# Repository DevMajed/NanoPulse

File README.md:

# NanoPulse – A Precision 24-bit Pulse Capture Digitizer
Hardware project — firmware will live in another repo.

# Purpose & Use Cases
**NanoPulse** is a 2-channel, 24-bit, trigger-synchronized digitizer for **µs-scale pulses**. It gives a cleaner, more deterministic “scope view” with higher vertical resolution, lower drift, and easy automation in a tiny form factor.
- What: 24-bit, 2-channel digitizer for µs pulses (hundreds of kHz BW).  
- For: labs validating pulse shape, battery DCIR, and rail transients, Ultrasonic/sonar echo logger (lab/test-tank, 40–300 kHz)
- Why: cleaner data than 8–12-bit scopes, deterministic trigger, tiny + scriptable.

---

# Purpose & Use Cases

**NanoPulse** delivers a deterministic external-trigger capture path tuned for **hundreds of kHz BW** and **µs pulses**.

## 1) Scope-replacement for pulsed benches (µs pulses)
**What it solves**  
Verify the **actual** applied pulse (rise/fall, overshoot, flatness, droop) without wheeling in a DSO.

**Who it’s for**  
Power-electronics / microwave labs, bench integrators.

**Hook**  
24-bit depth + clean CNV trigger reveals subtle flat-top errors and overshoot that 8–12-bit scopes smear.

**Connect (minimal extras)**
- `Sense Out (BNC/SMA)` → `NanoPulse IN` *(use a simple divider if needed)*
- `External Trigger (DDG/TTL)` → `TRIG IN` *(optional on-board 50 Ω)*

**Quick checklist**
- [ ] Minimal overshoot/ringing  
- [ ] Flat-top ripple/droop within spec  
- [ ] Repeated pulses overlay tightly (deterministic timing)

**Output**  
CSV + plots via simple Python scripts.

---

## 2) Battery / Cell DCIR & Pulsed-Load Logging
**What it solves**  
Clean capture of **voltage droop and relaxation** during programmed load pulses (≈10 µs–100 ms) for DCIR and transient analysis.

**Who it’s for**  
Battery research labs, EV startups, QA.

**Hook**  
High dynamic range + low drift → clearer droop and recovery curves than a typical scope; easy CSV export.

**Connect (minimal extras)**
- `Cell V` → `NanoPulse IN` *(add a 2-resistor divider if V exceeds input range)*  
- Optional: `Shunt V (current)` → `CH2`

**Quick checklist**
- [ ] Stable ΔV (droop) across repeats  
- [ ] Consistent relaxation time constants (τ)  
- [ ] Negligible baseline drift on long captures

**Output**  
CSV of V(t) (and I(t) if used), with auto-computed DCIR and τ.

---

## 3) Power-Rail / Load-Step Transient Verification (PMIC/LDO)
**What it solves**  
Measures **droop, settling time, and small ripple** on precision rails during load steps (≈100 µs–10 ms).

**Who it’s for**  
Analog/PMIC teams, embedded HW labs.

**Hook**  
24-bit vertical resolution + drift stability → see micro-ripple/settling that scopes miss.

**Connect (minimal extras)**
- `Rail` → `NanoPulse IN` *(use a small divider if needed)*  
- `Load-Step Trigger` → `TRIG IN` *(or use Manual Trigger)*

**Quick checklist**
- [ ] Droop within budget  
- [ ] No excessive undershoot/overshoot  
- [ ] Settling to ±x% within target time

**Output**  
CSV + auto-generated plot with annotated droop/settling metrics.

---

## 4) Ultrasonic / Sonar Echo Logging (lab/test-tank, 40–300 kHz)

**What it solves**  
Time-locked recording of **echo waveforms** for TOF, envelope, and multipath analysis—without touching OEM sonar firmware.

**Who it’s for**  
University acoustics/ultrasound labs, NDT benches, AUV/ROV research groups.

**Hook**  
24-bit dynamic range + deterministic trigger resolves **weak echoes** and small envelope changes better than typical 12–16-bit scopes.

**Connect (minimal extras)**
- `Receiver/Baseband Out (BNC/SMA)` → `NanoPulse IN` *(stay within input range or use a simple divider)*  
- `TX Sync/Trigger (TTL)` → `TRIG IN` *(optional on-board 50 Ω)*

**Quick checklist**
- [ ] Stable ping-to-echo timing (TOF) across repeats  
- [ ] Envelope + multipath clearly visible in the 40–300 kHz band  
- [ ] No clipping; baseline drift negligible on long logs

**Output**  
CSV of echo segments + optional envelope/spectrogram plots via Python.

---

# Headline Specs
- **ADC:** Analog Devices **AD4630-24**, up to **2 MSPS**, 24-bit  
- **Channels:** 2 differential, fully-differential amp (FDA) driven  
- **Trigger:** external **TRIG IN** → Schmitt-conditioned → CNV; **Manual Trigger** pad  
- **I/O domains:** **1.8 V** (ADC) and **3.3 V** (MCU) with level translators  
- **Reference:** **LTC6655-5** low-noise, low-drift  
- **Rails:** **LT3042** (+5.4 V), **LT3093** (−5.4 V), **LT1763** (1.8 V & 3.3 V)  
- **Configurable 50 Ω trigger termination** for DDG/coax use (DNP by default)

**Bandwidth envelope (typical build)**
- Usable analog BW: ~**300–600 kHz** (tunable via RCs)
- Practical “clean shape” pulse widths: **≥ 5–10 µs** (2 MSPS sampling)
- **Detect-only minimum pulse:** ~**1–2 µs** (1–2 samples)

---

# Design Highlights (Decisions & Rationale)
- **Anti-alias vs. settling (µs pulses in mind):** modest input Rs (~54 Ω) and small caps (≈1–2.7 nF) around the FDA target a **few-hundred-kHz to ~1 MHz** shaping—enough to see µs edges while improving settling and noise.
- **Low-drift reference path:** **LTC6655-5** with **10 µF + 0.1 µF** close to ADC REF minimizes baseline wander in long captures.
- **Trigger integrity:** External TRIG goes through a **Schmitt buffer + enable/OR logic** to produce a crisp **CNV**; **50 Ω** termination is **optional** for DDG/coax use.
- **Signal integrity at the converter:** **33 Ω series** per ADC input leg for damping; **22–33 Ω** on **CNV** after level translation to tame edges.
- **Clean domain split:** Translators isolate the quiet **1.8 V ADC** domain from **3.3 V MCU**, enabling fast SPI and **BUSY** handshaking.

---

## Trigger Modes
- **External-coax (DDG):** populate 50 Ω at TRIG IN; QC/DDG drives a matched line.  
- **Local-logic:** leave 50 Ω DNP; CNV is driven via translator with a **22–33 Ω** series resistor.

---

## Bring-Up Checklist
- **Power-only:** verify +5.4 V, −5.4 V, +3.3 V, +1.8 V rails; REF ≈ 5.000 V.  
- **CNV source:** confirm 3.3 V at Schmitt output and **1.8 V** at ADC CNV.  
- **Zero-volt short noise:** short IN+ to IN− at SMA; log RMS code spread.  
- **Step/edge:** feed a known step; confirm minimal ringing and proper settling.  
- **Drift:** shorted input, log ≥1 h; expect very low baseline drift.

---

## Safety & Limits
- Keep inputs **within safe range** (use passive dividers when needed).  
- Target content **≤ ~1 MHz** and **µs-scale** pulses.  
- For **ns edges/RF**, use a high-BW DSO/GHz digitizer.

---

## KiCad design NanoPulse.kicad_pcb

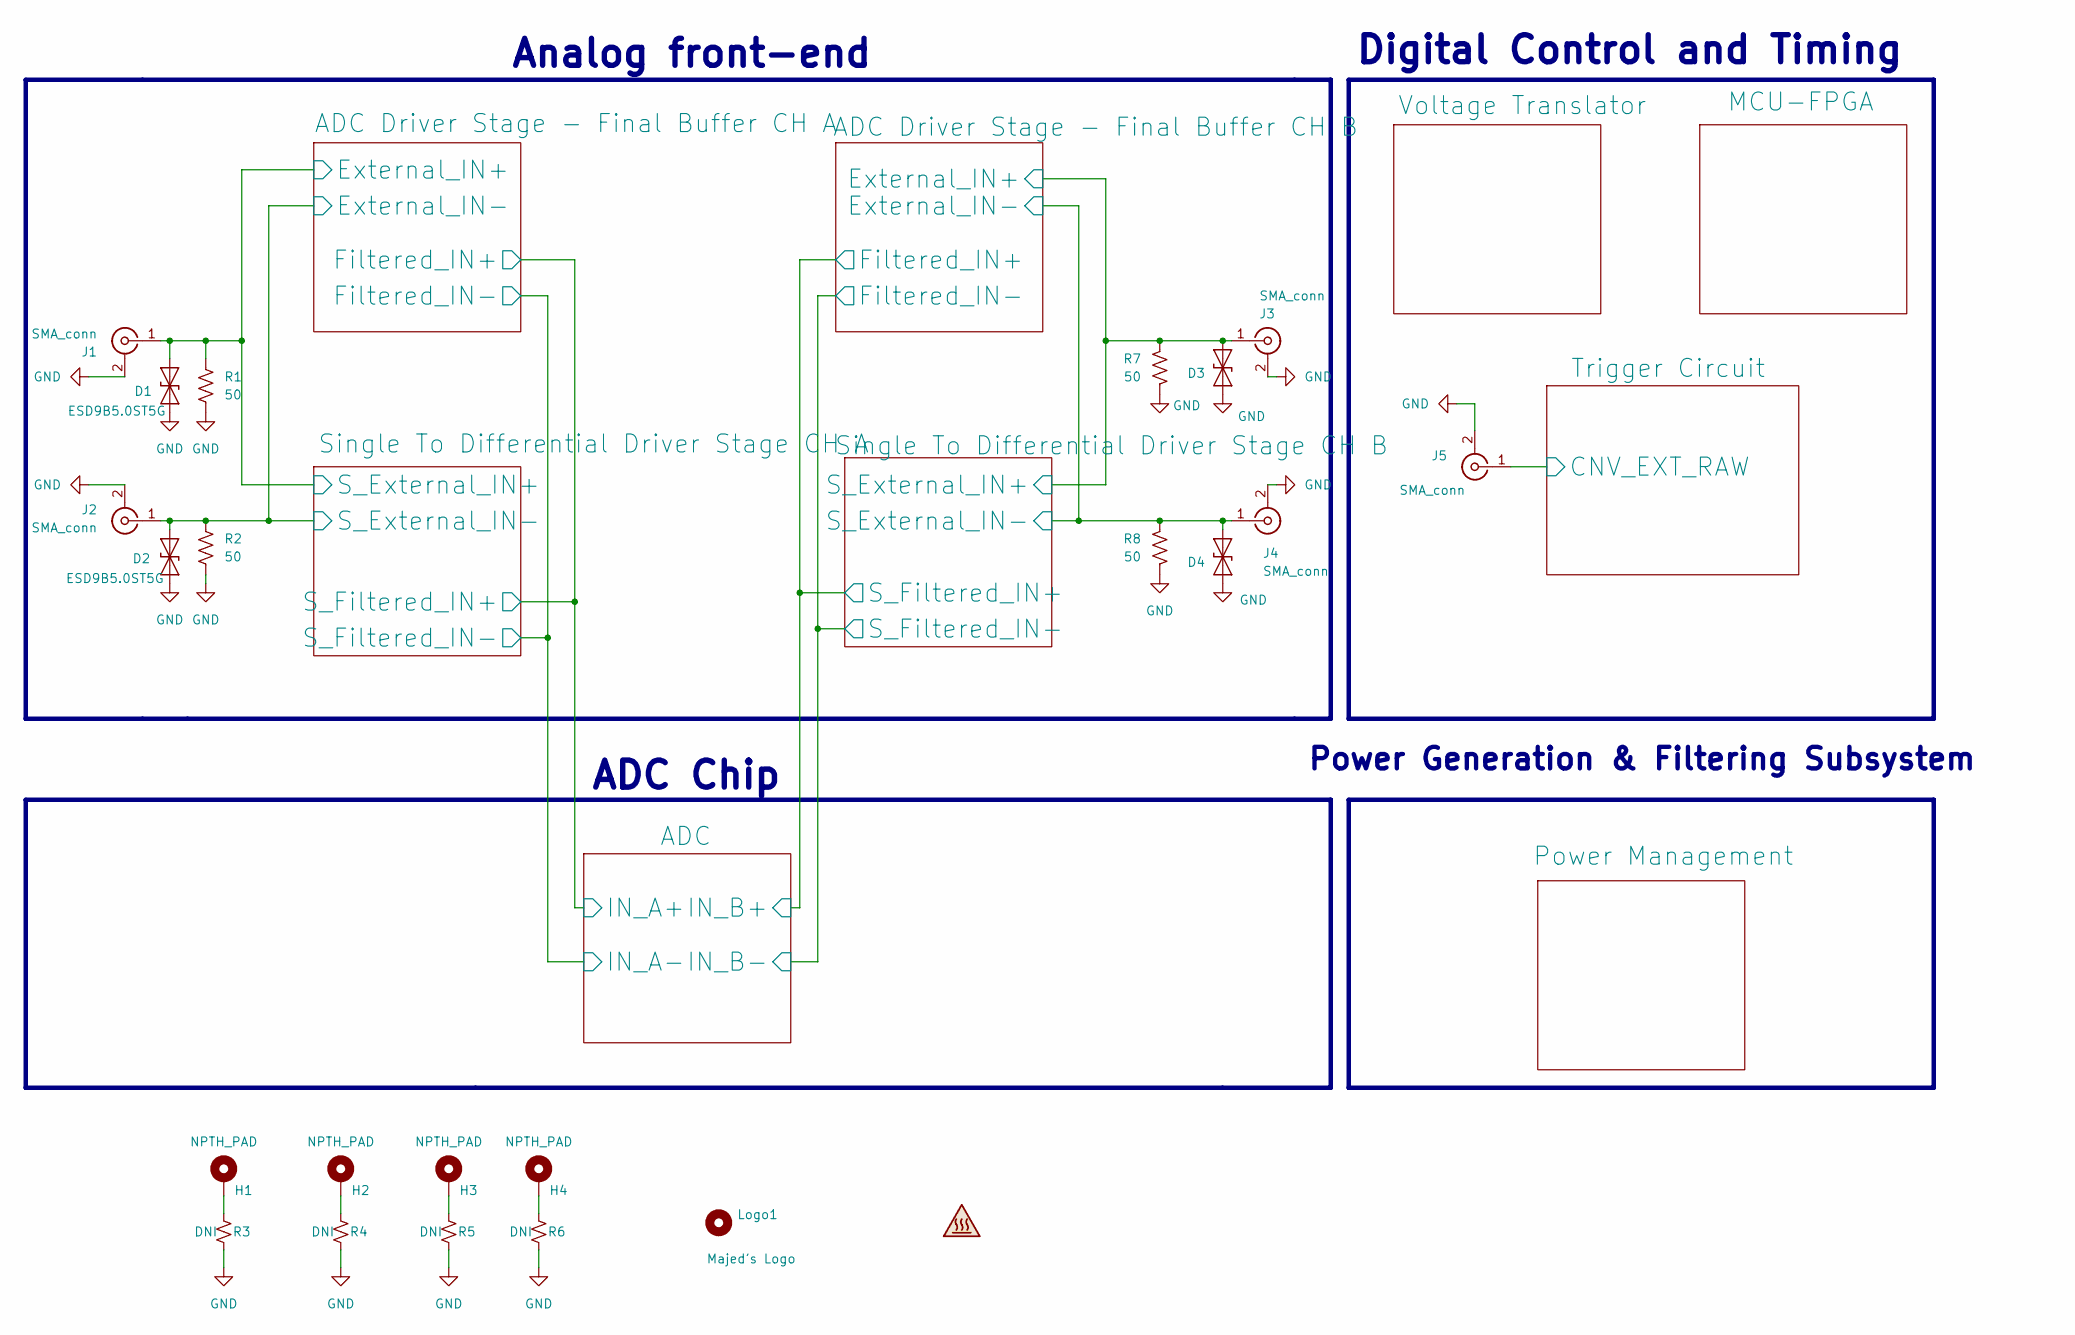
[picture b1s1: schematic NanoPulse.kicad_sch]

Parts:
D1, D2, D3, D4: ESD9B5.0ST5G; D_SOD-923; Mfg part # ESD9B5.0ST5G; Digikey ESD9B5.0ST5GOSCT-ND - Cut Tape
H1, H2, H3, H4: NPTH_PAD; Mounting_Wuerth_WA-SMSI-M1.6_H3.5mm_ThreadDepth2mm_NoNPTH_9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
J1, J2, J3, J4, J5: SMA_conn; SMA_Amphenol_132289_EdgeMount; Mfg part # 132289RP; Digikey ACX1427-ND
Logo1: Majed's Logo; Logo_Majed_small
R1, R2, R7, R8: 50; R_0603_1608Metric; Mfg part # RT0603BRE0750RL; Digikey 13-RT0603BRE0750RLCT-ND
R3, R4, R5, R6: DNI; R_0603_1608Metric

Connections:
/ADC Driver Stage - Final Buffer CH A/External_IN+: D1.2 (A2), J1.1 (In), R1.1; also elsewhere on the board
/ADC Driver Stage - Final Buffer CH A/External_IN-: D2.2 (A2), J2.1 (In), R2.1; also elsewhere on the board
/ADC Driver Stage - Final Buffer CH B/External_IN+: D3.2 (A2), J3.1 (In), R7.1; also elsewhere on the board
/ADC Driver Stage - Final Buffer CH B/External_IN-: D4.2 (A2), J4.1 (In), R8.1; also elsewhere on the board
/Trigger Circuit/CNV_EXT_RAW: J5.1 (In); also elsewhere on the board
GND: D1.1 (A1), D2.1 (A1), D3.1 (A1), D4.1 (A1), J1.2 (Ext), J2.2 (Ext), J3.2 (Ext), J4.2 (Ext), J5.2 (Ext), R1.2, R2.2, R3.1, R4.1, R5.1, R6.1, R7.2, R8.2; also elsewhere on the board
unnamed: H1.1, R3.2
unnamed: H2.1, R4.2
unnamed: H3.1, R5.2
unnamed: H4.1, R6.2

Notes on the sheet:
Power Generation & Filtering Subsystem
Digital Control and Timing
Analog front-end
ADC Chip

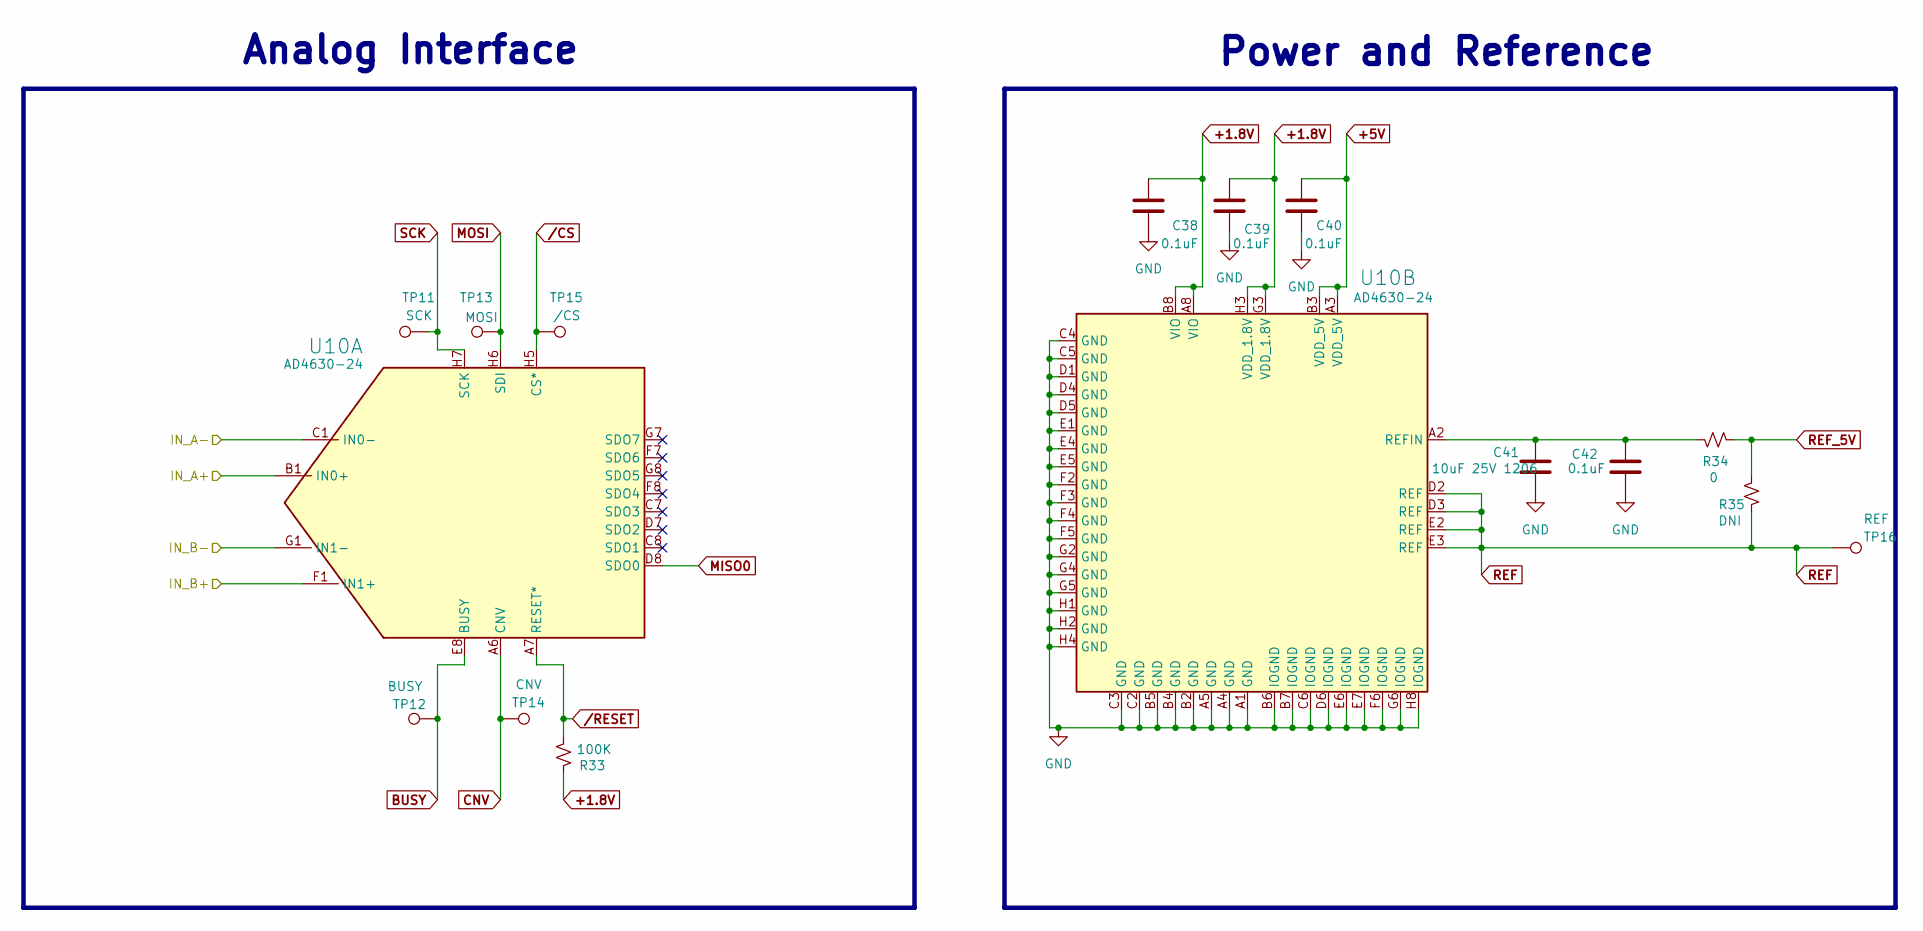
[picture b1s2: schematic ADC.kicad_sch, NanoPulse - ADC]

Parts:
C38, C39, C40, C42: 0.1uF; C_0603_1608Metric; Mfg part # CC0603KRX7R7BB104; Digikey 311-1088-1-ND
C41: 10uF 25V 1206; C_1206_3216Metric; Mfg part # CL31A106MAHNNNE; Digikey 1276-1181-1-ND
R33: 100K; R_0603_1608Metric; Mfg part # RC0603FR-07100KL; Digikey 311-100KHRCT-ND
R34: 0; R_0603_1608Metric; Mfg part # RC0603JR-070RL; Digikey 311-0.0GRCT-ND
R35: DNI; R_0603_1608Metric
TP11: SCK; TestPoint_Pad_1.0x1.0mm
TP12: BUSY; TestPoint_Pad_1.0x1.0mm
TP13: MOSI; TestPoint_Pad_1.0x1.0mm
TP14: CNV; TestPoint_Pad_1.0x1.0mm
TP15: /CS; TestPoint_Pad_1.0x1.0mm
TP16: REF; TestPoint_Pad_1.0x1.0mm
U10: AD4630-24; 05-08-1797_ADI-L; Mfg part # AD4630-24BBCZ-RL; Digikey 505-AD4630-24BBCZ-RLCT-ND

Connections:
+1.8V: C38.1, C39.1, R33.1, U10.A8 (VIO), U10.B8 (VIO), U10.G3 (VDD_1.8V), U10.H3 (VDD_1.8V); also elsewhere on the board
+5V: C40.1, U10.A3 (VDD_5V), U10.B3 (VDD_5V); also elsewhere on the board
/ADC Driver Stage - Final Buffer CH A/Filtered_IN+: U10.B1 (IN0+); also elsewhere on the board
/ADC Driver Stage - Final Buffer CH A/Filtered_IN-: U10.C1 (IN0-); also elsewhere on the board
/ADC Driver Stage - Final Buffer CH B/Filtered_IN+: U10.F1 (IN1+); also elsewhere on the board
/ADC Driver Stage - Final Buffer CH B/Filtered_IN-: U10.G1 (IN1-); also elsewhere on the board
BUSY: TP12.1, U10.E8 (BUSY); also elsewhere on the board
CNV: TP14.1, U10.A6 (CNV); also elsewhere on the board
GND: C38.2, C39.2, C40.2, C41.2, C42.2, U10.A1 (GND), U10.A4 (GND), U10.A5 (GND), U10.B2 (GND), U10.B4 (GND), U10.B5 (GND), U10.B6 (IOGND), U10.B7 (IOGND), U10.C2 (GND), U10.C3 (GND), U10.C4 (GND), U10.C5 (GND), U10.C6 (IOGND), U10.D1 (GND), U10.D4 (GND), U10.D5 (GND), U10.D6 (IOGND), U10.E1 (GND), U10.E4 (GND), U10.E5 (GND), U10.E6 (IOGND), U10.E7 (IOGND), U10.F2 (GND), U10.F3 (GND), U10.F4 (GND), U10.F5 (GND), U10.F6 (IOGND), U10.G2 (GND), U10.G4 (GND), U10.G5 (GND), U10.G6 (IOGND), U10.H1 (GND), U10.H2 (GND), U10.H4 (GND), U10.H8 (IOGND); also elsewhere on the board
MISO0: U10.D8 (SDO0); also elsewhere on the board
MOSI: TP13.1, U10.H6 (SDI); also elsewhere on the board
unnamed: C41.1, C42.1, R34.1, U10.A2 (REFIN)
REF: R35.2, TP16.1, U10.D2 (REF), U10.D3 (REF), U10.E2 (REF), U10.E3 (REF)
REF_5V: R34.2, R35.1; also elsewhere on the board
SCK: TP11.1, U10.H7 (SCK); also elsewhere on the board
/CS: TP15.1, U10.H5 (CS*); also elsewhere on the board
/RESET: R33.2, U10.A7 (RESET*); also elsewhere on the board

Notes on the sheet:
Analog Interface
Power and Reference

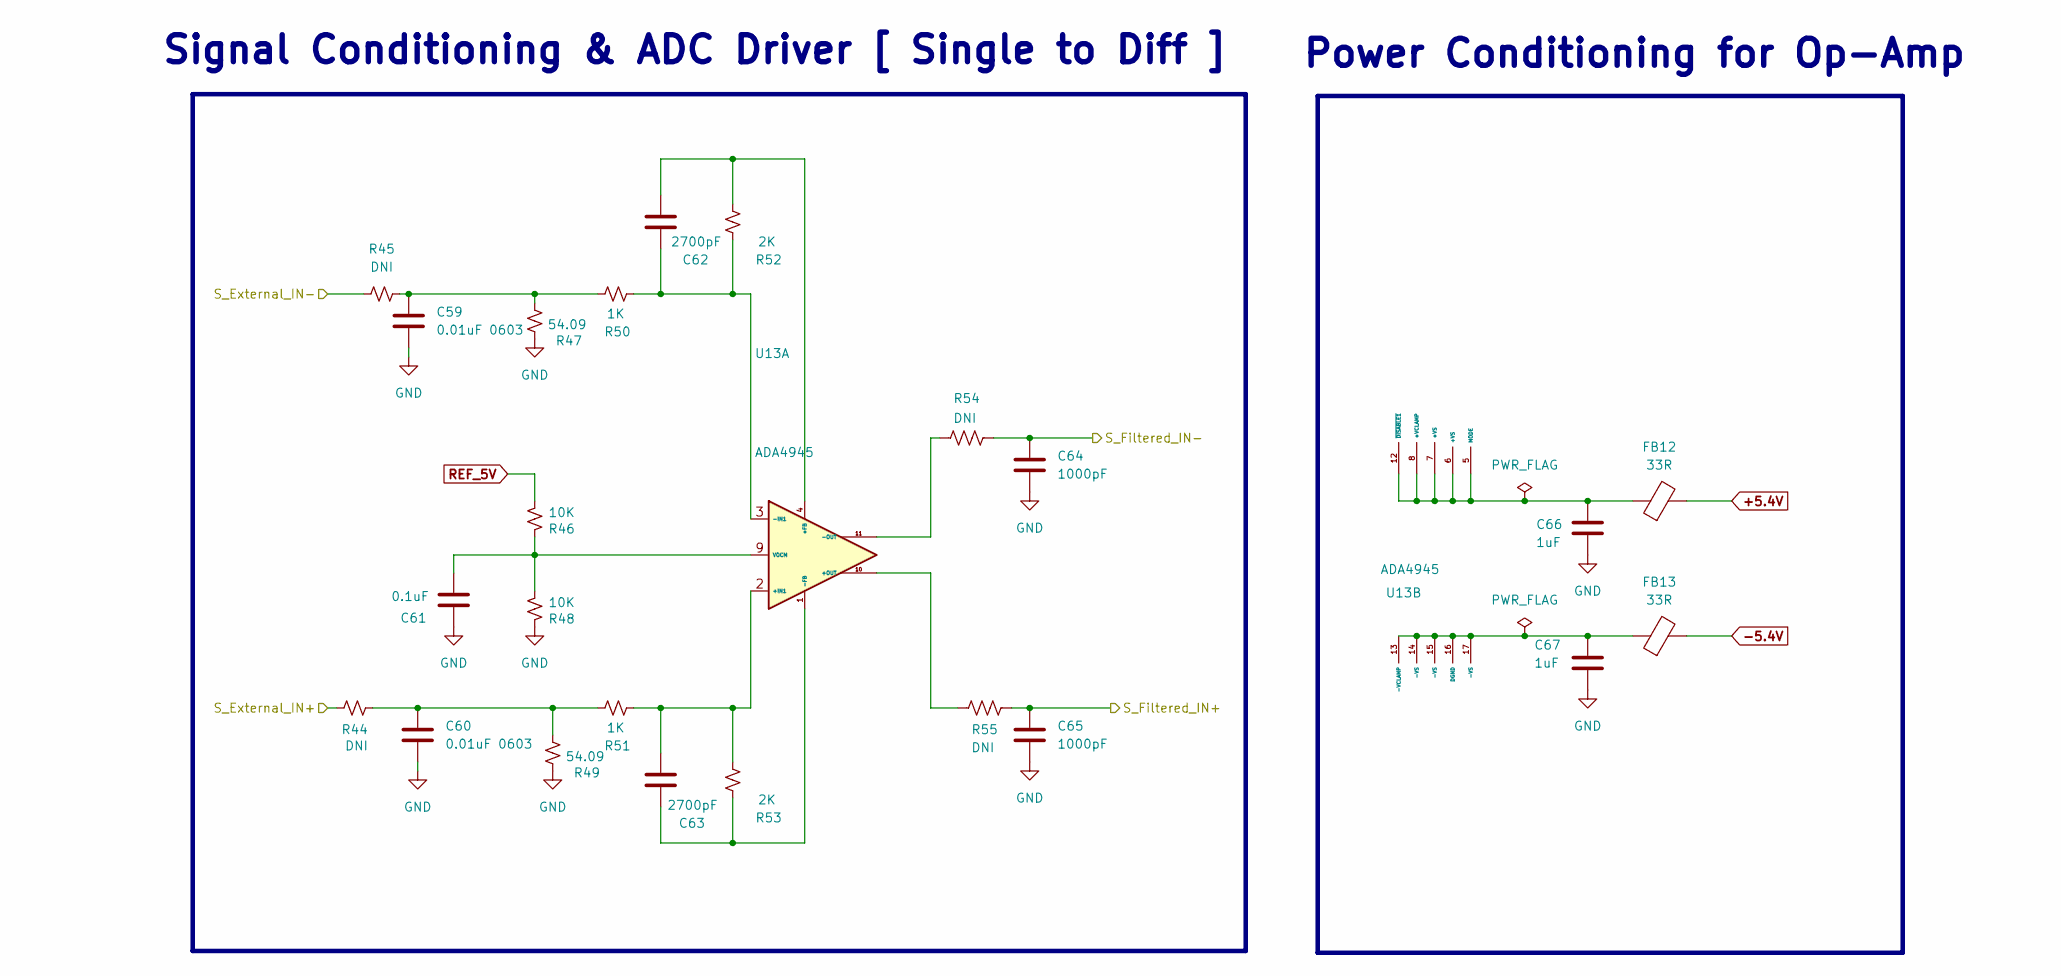
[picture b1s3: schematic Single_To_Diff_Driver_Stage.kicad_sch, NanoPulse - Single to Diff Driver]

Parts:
C59, C60: 0.01uF 0603; C_0603_1608Metric; Mfg part # C0603C103J5REC7411; Digikey 399-17568-1-ND
C61: 0.1uF; C_0603_1608Metric; Mfg part # CC0603KRX7R7BB104; Digikey 311-1088-1-ND
C62, C63: 2700pF; C_0805_2012Metric; Mfg part # CL21B272KBANNNC; Digikey 1276-2495-1-ND
C64, C65: 1000pF; C_0603_1608Metric; Mfg part # CL10B102KB8NNNC; Digikey 1276-1018-1-ND
C66, C67: 1uF; C_0603_1608Metric; Mfg part # CL10B105KP8NNNC; Digikey 1276-1946-1-ND
FB12, FB13: 33R; L_0603_1608Metric_Pad1.05x0.95mm_HandSolder; Mfg part # BLM18PG330SN1D; Digikey 490-5220-1-ND
R44, R45, R54, R55: DNI; R_0603_1608Metric
R46, R48: 10K; R_0603_1608Metric; Mfg part # RC0603FR-0710KL; Digikey 311-10.0KHRCT-ND
R47, R49: 54.09; R_0603_1608Metric; Mfg part # RC0603FR-0754R9L; Digikey 311-54.9HRCT-ND
R50, R51: 1K; R_0603_1608Metric; Mfg part # RC0603FR-071KL; Digikey 311-1.00KHRCT-ND
R52, R53: 2K; R_0603_1608Metric; Mfg part # RC0603FR-071KL; Digikey 311-2.00KHRCT-ND
U13: ADA4945; LFCSP16_ADA4945-1ACPZ-R2_ADI-L; Mfg part # ADA4945-1ACPZ-RL; Digikey 05-ADA4945-1ACPZ-RLCT-ND

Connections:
+5.4V: FB12.2; also elsewhere on the board
-5.4V: FB13.2; also elsewhere on the board
/ADC Driver Stage - Final Buffer CH A/External_IN+: R44.2; also elsewhere on the board
/ADC Driver Stage - Final Buffer CH A/External_IN-: R45.2; also elsewhere on the board
/ADC Driver Stage - Final Buffer CH A/Filtered_IN+: C65.1, R55.2; also elsewhere on the board
/ADC Driver Stage - Final Buffer CH A/Filtered_IN-: C64.1, R54.2; also elsewhere on the board
GND: C59.2, C60.2, C61.1, C64.2, C65.2, C66.2, C67.2, R47.2, R48.2, R49.2; also elsewhere on the board
unnamed: C59.1, R45.1, R47.1, R50.2
unnamed: C60.1, R44.1, R49.1, R51.2
unnamed: C62.2, R52.1, U13.4 (+FB)
unnamed: C63.2, R51.1, R53.1, U13.2 (+IN1)
unnamed: R55.1, U13.10 (+OUT)
unnamed: C63.1, R53.2, U13.1 (-FB)
unnamed: C62.1, R50.1, R52.2, U13.3 (-IN1)
unnamed: R54.1, U13.11 (-OUT)
unnamed: C61.2, R46.2, R48.1, U13.9 (VOCM)
unnamed: C66.1, FB12.1, U13.5 (MODE), U13.6 (+VS), U13.7 (+VS), U13.8 (+VCLAMP), U13.12 (~DISABLE1)
unnamed: C67.1, FB13.1, U13.13 (-VCLAMP), U13.14 (-VS), U13.15 (-VS), U13.16 (DGND), U13.17 (-VS)
REF_5V: R46.1; also elsewhere on the board

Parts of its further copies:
C68, C69: 0.01uF 0603; C_0603_1608Metric; Mfg part # C0603C103J5REC7411; Digikey 399-17568-1-ND
C70: 0.1uF; C_0603_1608Metric; Mfg part # CC0603KRX7R7BB104; Digikey 311-1088-1-ND
C71, C72: 2700pF; C_0805_2012Metric; Mfg part # CL21B272KBANNNC; Digikey 1276-2495-1-ND
C73, C74: 1000pF; C_0603_1608Metric; Mfg part # CL10B102KB8NNNC; Digikey 1276-1018-1-ND
C75, C76: 1uF; C_0603_1608Metric; Mfg part # CL10B105KP8NNNC; Digikey 1276-1946-1-ND
FB14, FB15: 33R; L_0603_1608Metric_Pad1.05x0.95mm_HandSolder; Mfg part # BLM18PG330SN1D; Digikey 490-5220-1-ND
R56, R57, R66, R67: DNI; R_0603_1608Metric
R58, R60: 10K; R_0603_1608Metric; Mfg part # RC0603FR-0710KL; Digikey 311-10.0KHRCT-ND
R59, R61: 54.09; R_0603_1608Metric; Mfg part # RC0603FR-0754R9L; Digikey 311-54.9HRCT-ND
R62, R63: 1K; R_0603_1608Metric; Mfg part # RC0603FR-071KL; Digikey 311-1.00KHRCT-ND
R64, R65: 2K; R_0603_1608Metric; Mfg part # RC0603FR-071KL; Digikey 311-2.00KHRCT-ND
U14: ADA4945; LFCSP16_ADA4945-1ACPZ-R2_ADI-L; Mfg part # ADA4945-1ACPZ-RL; Digikey 05-ADA4945-1ACPZ-RLCT-ND

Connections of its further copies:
+5.4V: FB14.2; also elsewhere on the board
-5.4V: FB15.2; also elsewhere on the board
/ADC Driver Stage - Final Buffer CH B/External_IN+: R56.2; also elsewhere on the board
/ADC Driver Stage - Final Buffer CH B/External_IN-: R57.2; also elsewhere on the board
/ADC Driver Stage - Final Buffer CH B/Filtered_IN+: C74.1, R67.2; also elsewhere on the board
/ADC Driver Stage - Final Buffer CH B/Filtered_IN-: C73.1, R66.2; also elsewhere on the board
GND: C68.2, C69.2, C70.1, C73.2, C74.2, C75.2, C76.2, R59.2, R60.2, R61.2; also elsewhere on the board
unnamed: C68.1, R57.1, R59.1, R62.2
unnamed: C69.1, R56.1, R61.1, R63.2
unnamed: C71.2, R64.1, U14.4 (+FB)
unnamed: C72.2, R63.1, R65.1, U14.2 (+IN1)
unnamed: R67.1, U14.10 (+OUT)
unnamed: C72.1, R65.2, U14.1 (-FB)
unnamed: C71.1, R62.1, R64.2, U14.3 (-IN1)
unnamed: R66.1, U14.11 (-OUT)
unnamed: C70.2, R58.2, R60.1, U14.9 (VOCM)
unnamed: C75.1, FB14.1, U14.5 (MODE), U14.6 (+VS), U14.7 (+VS), U14.8 (+VCLAMP), U14.12 (~DISABLE1)
unnamed: C76.1, FB15.1, U14.13 (-VCLAMP), U14.14 (-VS), U14.15 (-VS), U14.16 (DGND), U14.17 (-VS)
REF_5V: R58.1; also elsewhere on the board

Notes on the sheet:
Power Conditioning for Op-Amp
Signal Conditioning & ADC Driver [ Single to Diff ]

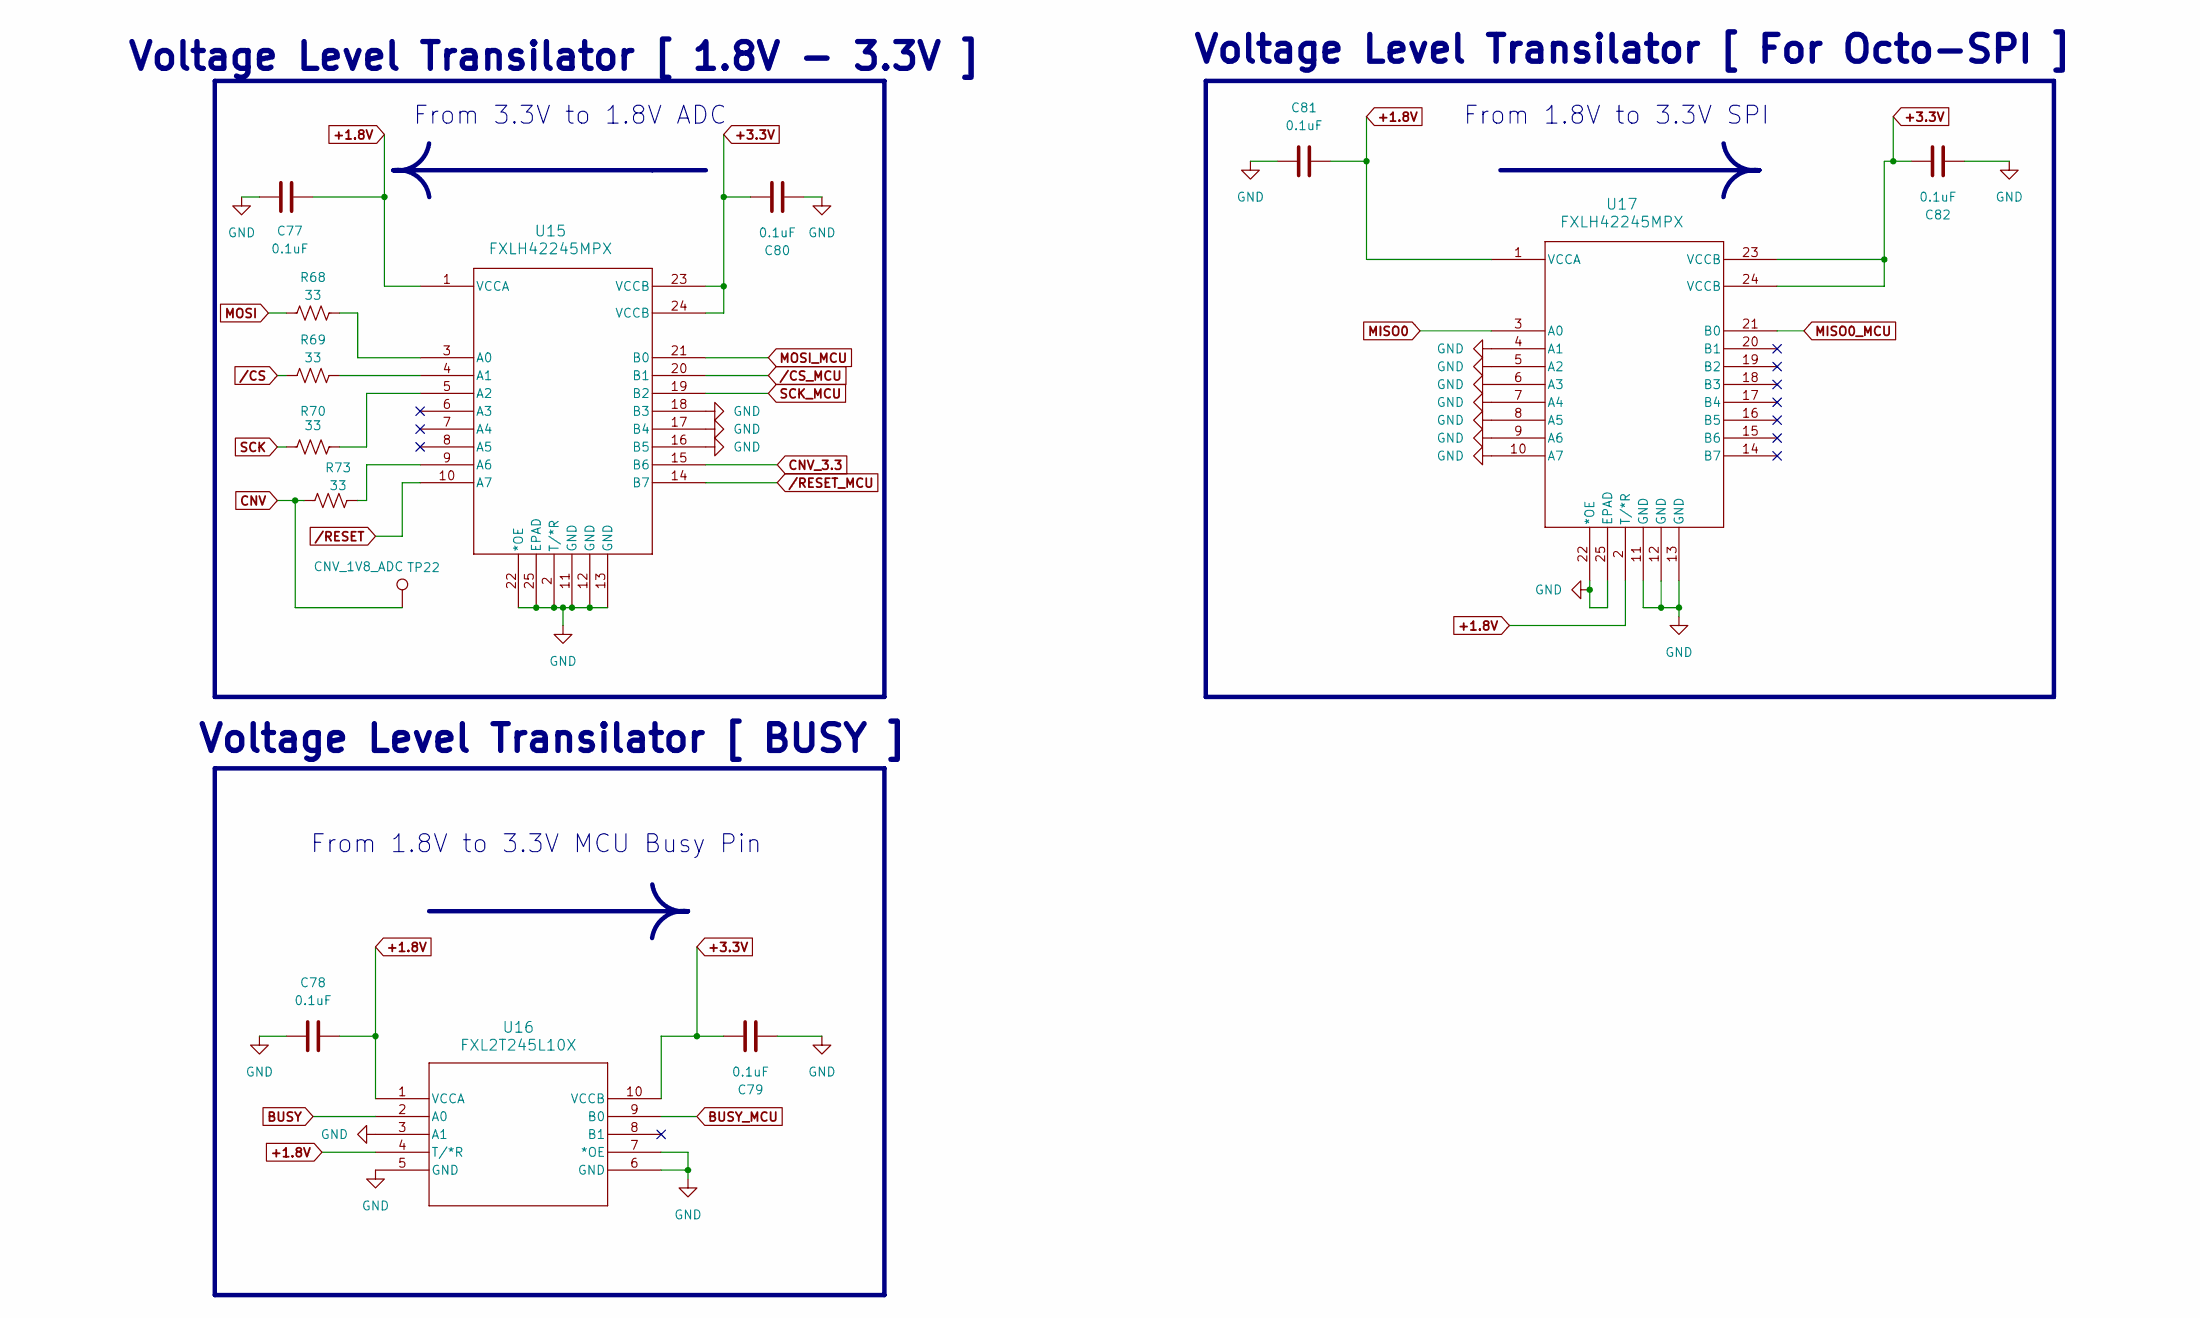
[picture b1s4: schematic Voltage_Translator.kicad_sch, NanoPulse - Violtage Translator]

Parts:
C77, C78, C79, C80, C81, C82: 0.1uF; C_0603_1608Metric; Mfg part # CC0603KRX7R7BB104; Digikey 311-1088-1-ND
R68, R69, R70, R73: 33; R_0603_1608Metric; Mfg part # RC0603FR-072KL; Digikey 311-33GRCT-ND
TP22: CNV_1V8_ADC; TestPoint_Pad_1.0x1.0mm
U15, U17: FXLH42245MPX; MLP24_4P5X3P5_ONS; Mfg part # FXLH42245MPX; Digikey FXLH42245MPXCT-ND
U16: FXL2T245L10X; MICROPAK10_2P1X1P6_ONS-L; Mfg part # FXL2T245L10X; Digikey FXL2T245L10XCT-ND

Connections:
+1.8V: C77.1, C78.1, C81.1, U15.1 (VCCA), U16.1 (VCCA), U16.4 (T/*R), U17.1 (VCCA), U17.2 (T/*R); also elsewhere on the board
+3.3V: C79.1, C80.1, C82.1, U15.23 (VCCB), U15.24 (VCCB), U16.10 (VCCB), U17.23 (VCCB), U17.24 (VCCB); also elsewhere on the board
BUSY: U16.2 (A0); also elsewhere on the board
BUSY_MCU: U16.9 (B0); also elsewhere on the board
CNV: R73.2, TP22.1; also elsewhere on the board
CNV_3.3: U15.15 (B6); also elsewhere on the board
GND: C77.2, C78.2, C79.2, C80.2, C81.2, C82.2, U15.2 (T/*R), U15.11 (GND), U15.12 (GND), U15.13 (GND), U15.16 (B5), U15.17 (B4), U15.18 (B3), U15.22 (*OE), U15.25 (EPAD), U16.3 (A1), U16.5 (GND), U16.6 (GND), U16.7 (*OE), U17.4 (A1), U17.5 (A2), U17.6 (A3), U17.7 (A4), U17.8 (A5), U17.9 (A6), U17.10 (A7), U17.11 (GND), U17.12 (GND), U17.13 (GND), U17.22 (*OE), U17.25 (EPAD); also elsewhere on the board
MISO0: U17.3 (A0); also elsewhere on the board
MISO0_MCU: U17.21 (B0); also elsewhere on the board
MOSI: R68.1; also elsewhere on the board
MOSI_MCU: U15.21 (B0); also elsewhere on the board
unnamed: R68.2, U15.3 (A0)
unnamed: R69.2, U15.4 (A1)
unnamed: R70.2, U15.5 (A2)
unnamed: R73.1, U15.9 (A6)
SCK: R70.1; also elsewhere on the board
SCK_MCU: U15.19 (B2); also elsewhere on the board
/CS: R69.1; also elsewhere on the board
/CS_MCU: U15.20 (B1); also elsewhere on the board
/RESET: U15.10 (A7); also elsewhere on the board
/RESET_MCU: U15.14 (B7); also elsewhere on the board

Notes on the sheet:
Voltage Level Transilator [ BUSY ]
Voltage Level Transilator [ 1.8V - 3.3V ]
Voltage Level Transilator [ For Octo-SPI ]
From 3.3V to 1.8V ADC
From 1.8V to 3.3V MCU Busy Pin
From 1.8V to 3.3V SPI

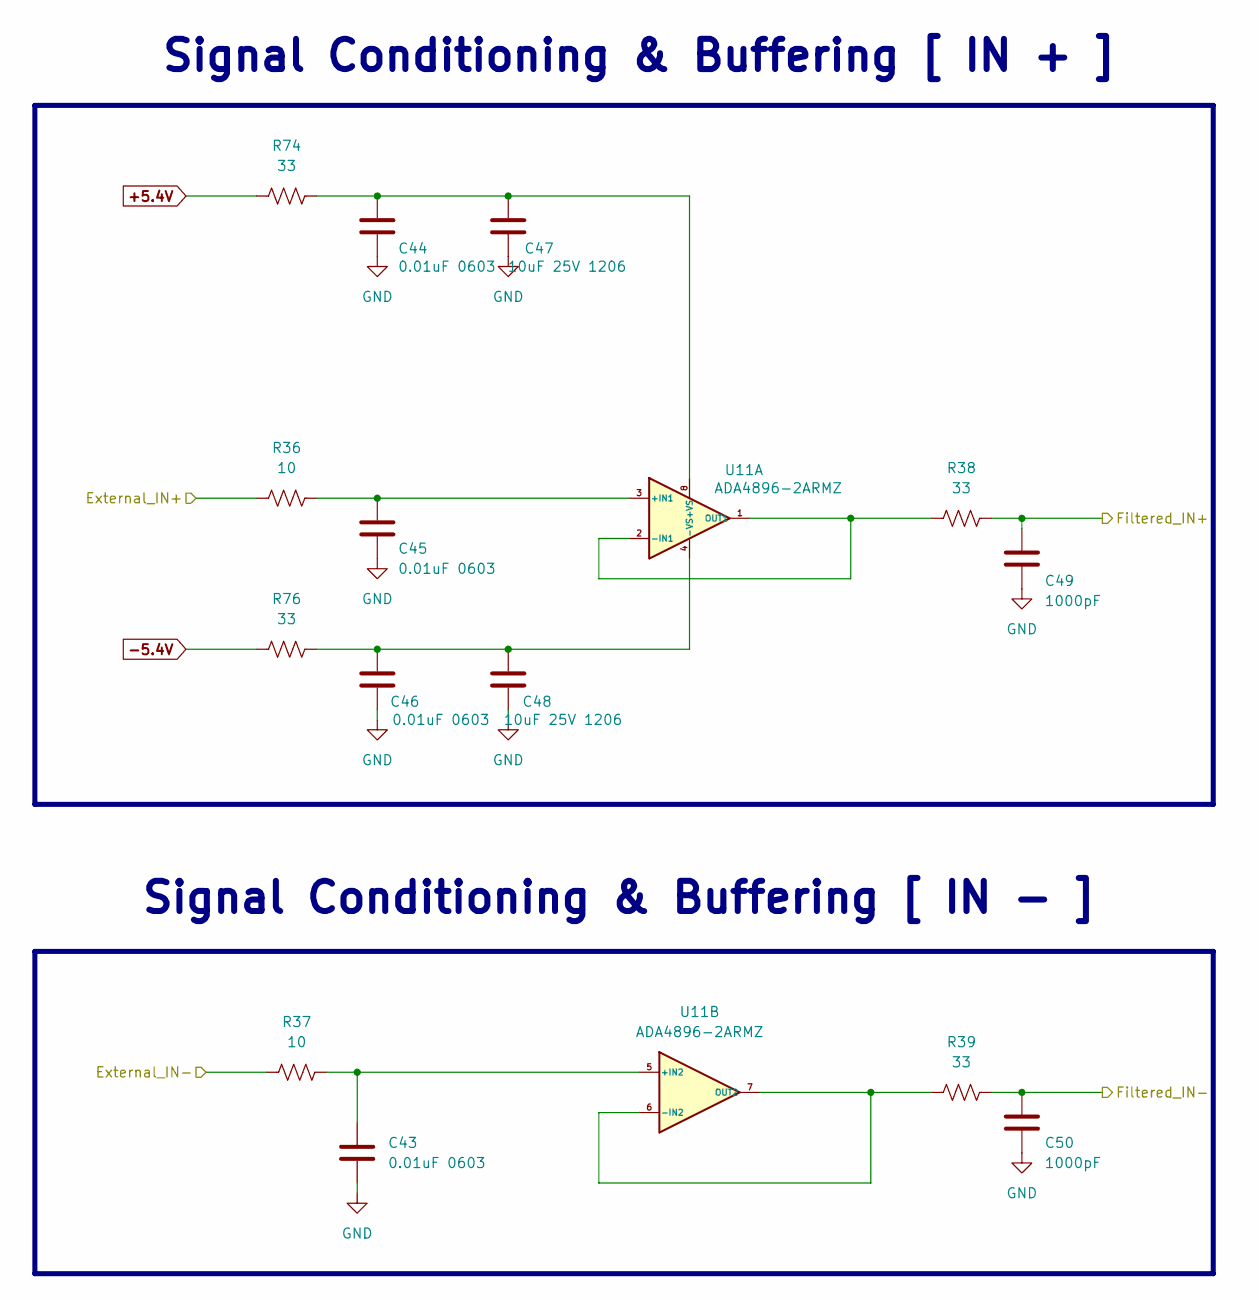
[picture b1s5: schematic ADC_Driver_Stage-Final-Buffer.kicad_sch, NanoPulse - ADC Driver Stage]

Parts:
C43, C44, C45, C46: 0.01uF 0603; C_0603_1608Metric; Mfg part # C0603C103J5REC7411; Digikey 399-17568-1-ND
C47, C48: 10uF 25V 1206; C_1206_3216Metric; Mfg part # CL31A106MAHNNNE; Digikey 1276-1181-1-ND
C49, C50: 1000pF; C_0603_1608Metric; Mfg part # CL10B102KB8NNNC; Digikey 1276-1018-1-ND
R36, R37: 10; R_0805_2012Metric; Mfg part # RC0805FR-0710RL; Digikey 311-10.0CRCT-ND
R38, R39, R74, R76: 33; R_0603_1608Metric; Mfg part # RC0603FR-072KL; Digikey 311-33GRCT-ND
U11: ADA4896-2ARMZ; RM_8_ADI; Mfg part # ADA4896-2ARMZ; Digikey 505-ADA4896-2ARMZ-ND

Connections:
+5.4V: R74.2; also elsewhere on the board
-5.4V: R76.2; also elsewhere on the board
/ADC Driver Stage - Final Buffer CH A/External_IN+: R36.1; also elsewhere on the board
/ADC Driver Stage - Final Buffer CH A/External_IN-: R37.2; also elsewhere on the board
/ADC Driver Stage - Final Buffer CH A/Filtered_IN+: C49.1, R38.1; also elsewhere on the board
/ADC Driver Stage - Final Buffer CH A/Filtered_IN-: C50.1, R39.1; also elsewhere on the board
GND: C43.2, C44.2, C45.2, C46.2, C47.2, C48.2, C49.2, C50.2; also elsewhere on the board
unnamed: C45.1, R36.2, U11.3 (+IN1)
unnamed: C44.1, C47.1, R74.1, U11.8 (+VS)
unnamed: R38.2, U11.1 (OUT1), U11.2 (-IN1)
unnamed: C46.1, C48.1, R76.1, U11.4 (-VS)
unnamed: C43.1, R37.1, U11.5 (+IN2)
unnamed: R39.2, U11.6 (-IN2), U11.7 (OUT2)

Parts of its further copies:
C51, C52, C53, C54: 0.01uF 0603; C_0603_1608Metric; Mfg part # C0603C103J5REC7411; Digikey 399-17568-1-ND
C55, C56: 10uF 25V 1206; C_1206_3216Metric; Mfg part # CL31A106MAHNNNE; Digikey 1276-1181-1-ND
C57, C58: 1000pF; C_0603_1608Metric; Mfg part # CL10B102KB8NNNC; Digikey 1276-1018-1-ND
R40, R41: 10; R_0805_2012Metric; Mfg part # RC0805FR-0710RL; Digikey 311-10.0CRCT-ND
R42, R43, R75, R77: 33; R_0603_1608Metric; Mfg part # RC0603FR-072KL; Digikey 311-33GRCT-ND
U12: ADA4896-2ARMZ; RM_8_ADI; Mfg part # ADA4896-2ARMZ; Digikey 505-ADA4896-2ARMZ-ND

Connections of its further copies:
+5.4V: R75.2; also elsewhere on the board
-5.4V: R77.2; also elsewhere on the board
/ADC Driver Stage - Final Buffer CH B/External_IN+: R40.1; also elsewhere on the board
/ADC Driver Stage - Final Buffer CH B/External_IN-: R41.2; also elsewhere on the board
/ADC Driver Stage - Final Buffer CH B/Filtered_IN+: C57.1, R42.1; also elsewhere on the board
/ADC Driver Stage - Final Buffer CH B/Filtered_IN-: C58.1, R43.1; also elsewhere on the board
GND: C51.2, C52.2, C53.2, C54.2, C55.2, C56.2, C57.2, C58.2; also elsewhere on the board
unnamed: C53.1, R40.2, U12.3 (+IN1)
unnamed: C52.1, C55.1, R75.1, U12.8 (+VS)
unnamed: R42.2, U12.1 (OUT1), U12.2 (-IN1)
unnamed: C54.1, C56.1, R77.1, U12.4 (-VS)
unnamed: C51.1, R41.1, U12.5 (+IN2)
unnamed: R43.2, U12.6 (-IN2), U12.7 (OUT2)

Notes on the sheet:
Signal Conditioning & Buffering [ IN + ]
Signal Conditioning & Buffering [ IN - ]
